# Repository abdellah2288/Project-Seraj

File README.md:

# Project-Seraj
An Open source development board for EHTP ElectroPower's Circuit Jam Hackathon ([Schematics](https://github.com/abdellah2288/Project-Seraj/files/14251244/seraj.pdf))

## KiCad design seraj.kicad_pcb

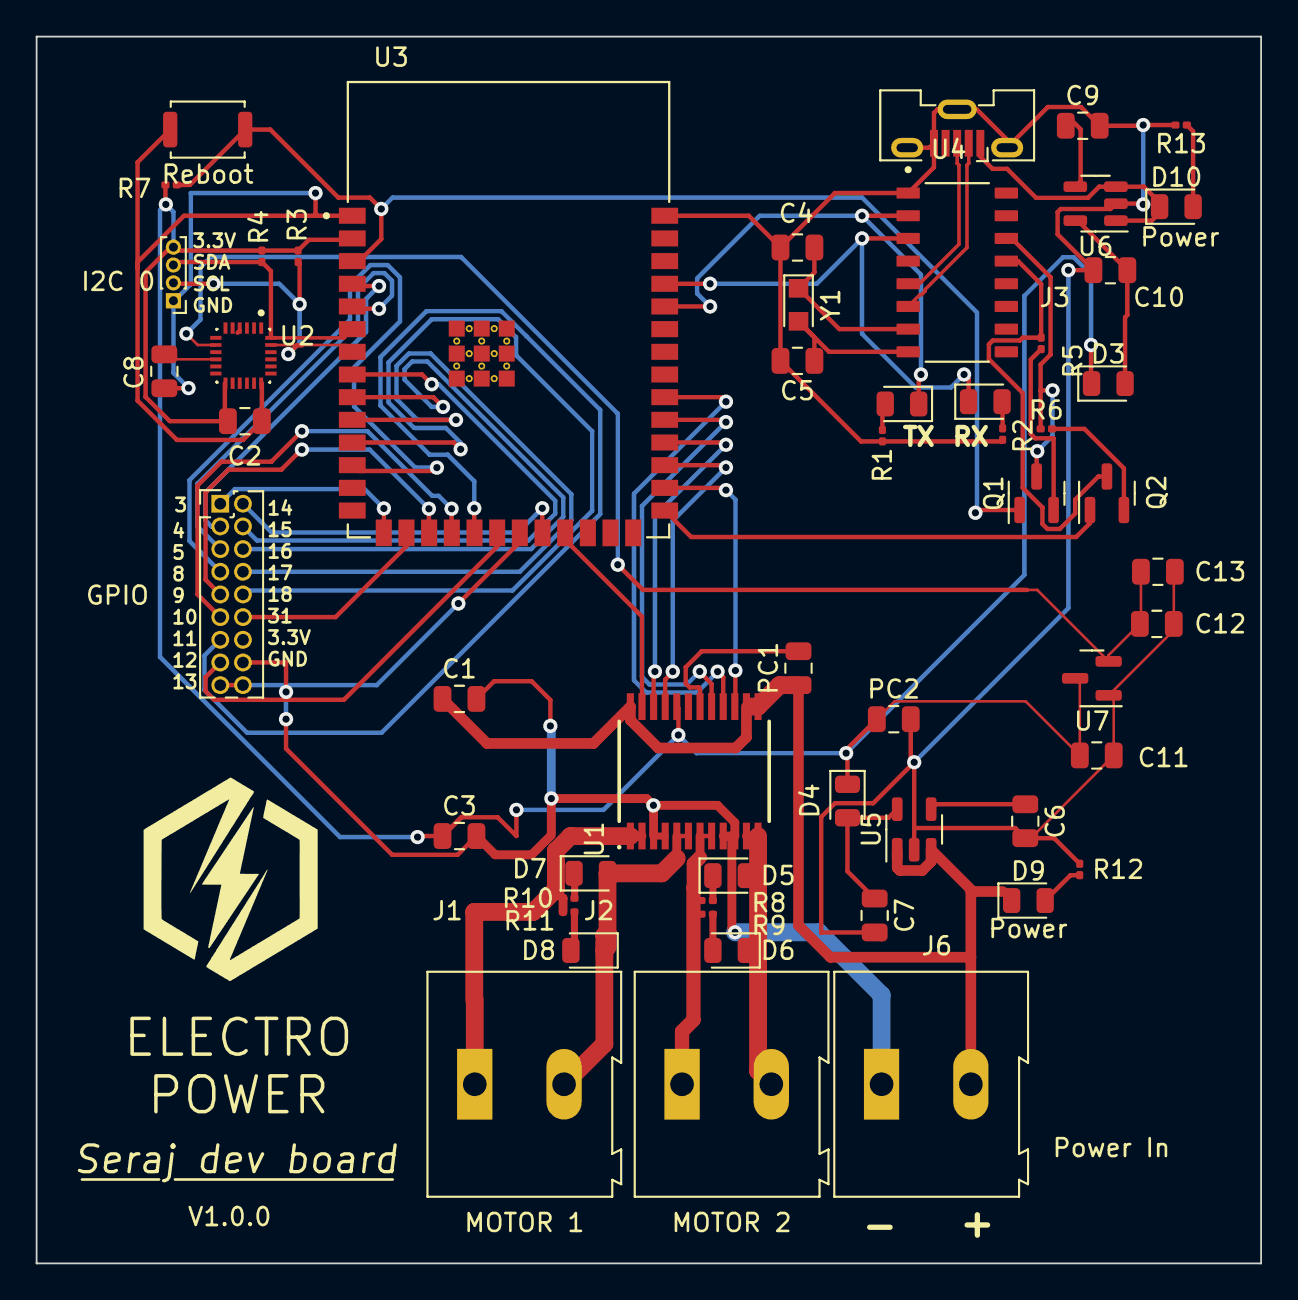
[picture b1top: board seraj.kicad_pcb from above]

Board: 2 copper layers, 68.6 x 68.7 mm, 55 parts (0 on the bottom side), 55 nets.

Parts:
C1, C2, C3, C8, C13: 0.1uF; C_0805_2012Metric
C4, C5: 22pF; C_0805_2012Metric
C6, C9: 470pF; C_0805_2012Metric
C7, C10: 2.2uF; C_0805_2012Metric
C11, C12: 1uF; C_0805_2012Metric
D1, D2, D5, D6, D7, D8, D9, D10: LED; LED_0805_2012Metric
D3, D4: 1N5819HW-7-F; D_0805_2012Metric
J1: MOTOR 1; TerminalBlock_Altech_AK300-2_P5.00mm
J2: MOTOR 2; TerminalBlock_Altech_AK300-2_P5.00mm
J3: Serial; USB_Micro-B_Molex-105133-0031
J4: I2C 0; PinHeader_1x04_P1.00mm_Vertical
J5: Conn_2Rows-17Pins; PinHeader_2x09_P1.27mm_Vertical
J6: Power In; TerminalBlock_Altech_AK300-2_P5.00mm
PC1, PC2: 10uF; C_0805_2012Metric
Q1, Q2: NPN; SOT-23
R1, R2, R3, R4, R7: 4.7k; R_0201_0603Metric
R5, R6: 12k; R_0201_0603Metric
R8, R9, R10, R11, R12, R13: 10k; R_0201_0603Metric
SW1: Reboot; SW_Push_SPST_NO_Alps_SKRK
U1: TB6612FNG_C_8_EL; SOP65P760X160-24N
U2: ICM-20948; QFN40P300X300X105-24N
U3: ESP32-S3-WROOM-1-N8R8; XCVR_ESP32S3WROOM1N8R8
U4: CH340G; SOIC127P600X180-16N
U5, U6: MIC5219-3.6YM5; SOT-23-5
U7: MCP1700x-120xxTT; SOT-23
Y1: 12MHz; Crystal_SMD_2012-2Pin_2.0x1.2mm_HandSoldering

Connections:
+1V8: C12.1, C13.1, U2.8 (VDDIO), U7.2 (VO)
+3.3V: C2.1, C3.1, C11.1, D3.1 (K), D4.1 (K), J4.4, PC2.1, R3.1, R4.1, R7.1, U1.20 (VCC), U2.13 (VDD), U3.2 (3V3), U7.3 (VI)
+12V: C1.1, D9.1 (K), J6.2, PC1.1, U1.13 (VM2), U1.14 (VM3), U1.24 (VM1), U5.1 (IN), U5.3 (EN)
/AIN1: U1.21 (AIN1), U3.29 (IO36)
/AIN2: U1.22 (AIN2), U3.30 (IO37)
/BIN1: U1.17 (BIN1), U3.31 (IO38)
/BIN2: U1.16 (BIN2), U3.32 (IO39)
/BOOT: Q2.1 (C), U3.27 (IO0)
/DTR#: Q2.3 (E), R5.1, U4.13 (~DTR)
/EN: Q1.1 (C), R7.2, SW1.2, U3.3 (EN)
/GPIO3: J5.1, U3.15 (IO3)
/GPIO4: J5.3, U3.4 (IO4)
/GPIO5: J5.5, U3.5 (IO5)
/GPIO8: J5.7, U3.12 (IO8)
/GPIO9: J5.9, U3.17 (IO9)
/GPIO10: J5.11, U3.18 (IO10)
/GPIO11: J5.13, U3.19 (IO11)
/GPIO14: J5.2, U3.22 (IO14)
/GPIO15: J5.4, U3.8 (IO15)
/GPIO16: J5.6, U3.9 (IO16)
/GPIO17: J5.8, U3.10 (IO17)
/GPIO18: J5.10, U3.11 (IO18)
/GPIO31: J5.12, U3.16 (IO46)
/PWMA: U1.23 (PWMA), U3.23 (IO21)
/PWMB: U1.15 (PWMB), U3.28 (IO35)
/RTS#: Q1.3 (E), R6.1, U4.14 (~RTS)
/SCL_0: J4.2, R3.2, U2.23 (SCL/SCLK), U3.7 (IO7)
/SDA_0: J4.3, R4.2, U2.24 (SDA/SDI), U3.6 (IO6)
/Serial_D+: J3.3 (D+), U4.5 (UD+)
/Serial_D-: J3.2 (D-), U4.6 (UD-)
/Serial_RX: D2.1 (K), U3.37 (TXD0), U4.3 (RXD)
/Serial_TX: D1.1 (K), U3.36 (RXD0), U4.2 (TXD)
GND: C1.2, C2.2, C3.2, C4.2, C5.2, C6.2, C7.2, C8.2, C9.2, C10.2, C11.2, C12.2, C13.2, J3.5 (GND), J3.6 (Shield), J4.1, J5.15, J5.16, J5.17, J5.18, J6.1, PC1.2, PC2.2, R1.2, R2.2, R12.2, R13.2, SW1.1, U1.3 (PGND1@1), U1.4 (PGND1@2), U1.9 (PGND2@1), U1.10 (PGND2@2), U1.18 (GND), U2.18 (GND), U3.1 (GND), U3.20 (IO12), U3.21 (IO13), U3.40 (GND), U3.41_1 (GND), U3.41_2 (GND), U3.41_3 (GND), U3.41_4 (GND), U3.41_5 (GND), U3.41_6 (GND), U3.41_7 (GND), U3.41_8 (GND), U3.41_9 (GND), U4.1 (GND), U5.2 (GND), U6.2 (GND), U7.1 (GND)
unnamed: D1.2 (A), R1.1
unnamed: D2.2 (A), R2.1
unnamed: C10.1, D3.2 (A), U6.5 (OUT)
unnamed: C7.1, D4.2 (A), U5.5 (OUT)
unnamed: D5.2 (A), D6.1 (K), J2.2, U1.11 (BO1@1), U1.12 (BO1@2)
unnamed: D5.1 (K), R8.2
unnamed: D6.2 (A), R9.2
unnamed: D7.2 (A), D8.1 (K), J1.2, U1.5 (AO2@1), U1.6 (AO2@2)
unnamed: D7.1 (K), R10.2
unnamed: D8.2 (A), R11.2
unnamed: D9.2 (A), R12.1
unnamed: D10.2 (A), R13.1
unnamed: J1.1, R10.1, R11.1, U1.1 (AO1@1), U1.2 (AO1@2)
unnamed: J2.1, R8.1, R9.1, U1.7 (BO2@1), U1.8 (BO2@2)
unnamed: Q1.2 (B), R5.2
unnamed: Q2.2 (B), R6.2
unnamed: C8.1, U2.10 (REGOUT)
unnamed: C4.1, U4.7 (XI), Y1.1
unnamed: C5.1, U4.8 (XO), Y1.2
unnamed: C6.1, U5.4 (BP)
unnamed: C9.1, U6.4 (BP)
VBUS: D10.1 (K), J3.1 (VBUS), U6.1 (IN), U6.3 (EN)

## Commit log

2024-02-12 Uploaded Design Files.
